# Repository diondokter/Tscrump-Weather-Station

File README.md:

# Tscrump-Weather-Station
Project for making a weather station.

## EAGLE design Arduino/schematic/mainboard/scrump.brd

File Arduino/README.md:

The bootloader is the exact same as the Adafruit M0 feather.
You will need to install the SAMD board toolchain from Adafruit in your Arduino IDE to compile and upload.
Instructions can be found [here](https://learn.adafruit.com/adafruit-feather-m0-basic-proto/using-with-arduino-ide).

You will need the following libraries:
- TheThingsNetwork 2.0.0 (2.1+ breaks non-AVR compatibility)
- Adafruit Unified Sensor 1.0.2
- DHT sensor library 1.3.0+
- Adafruit BMP085 Unified 1.0.0+

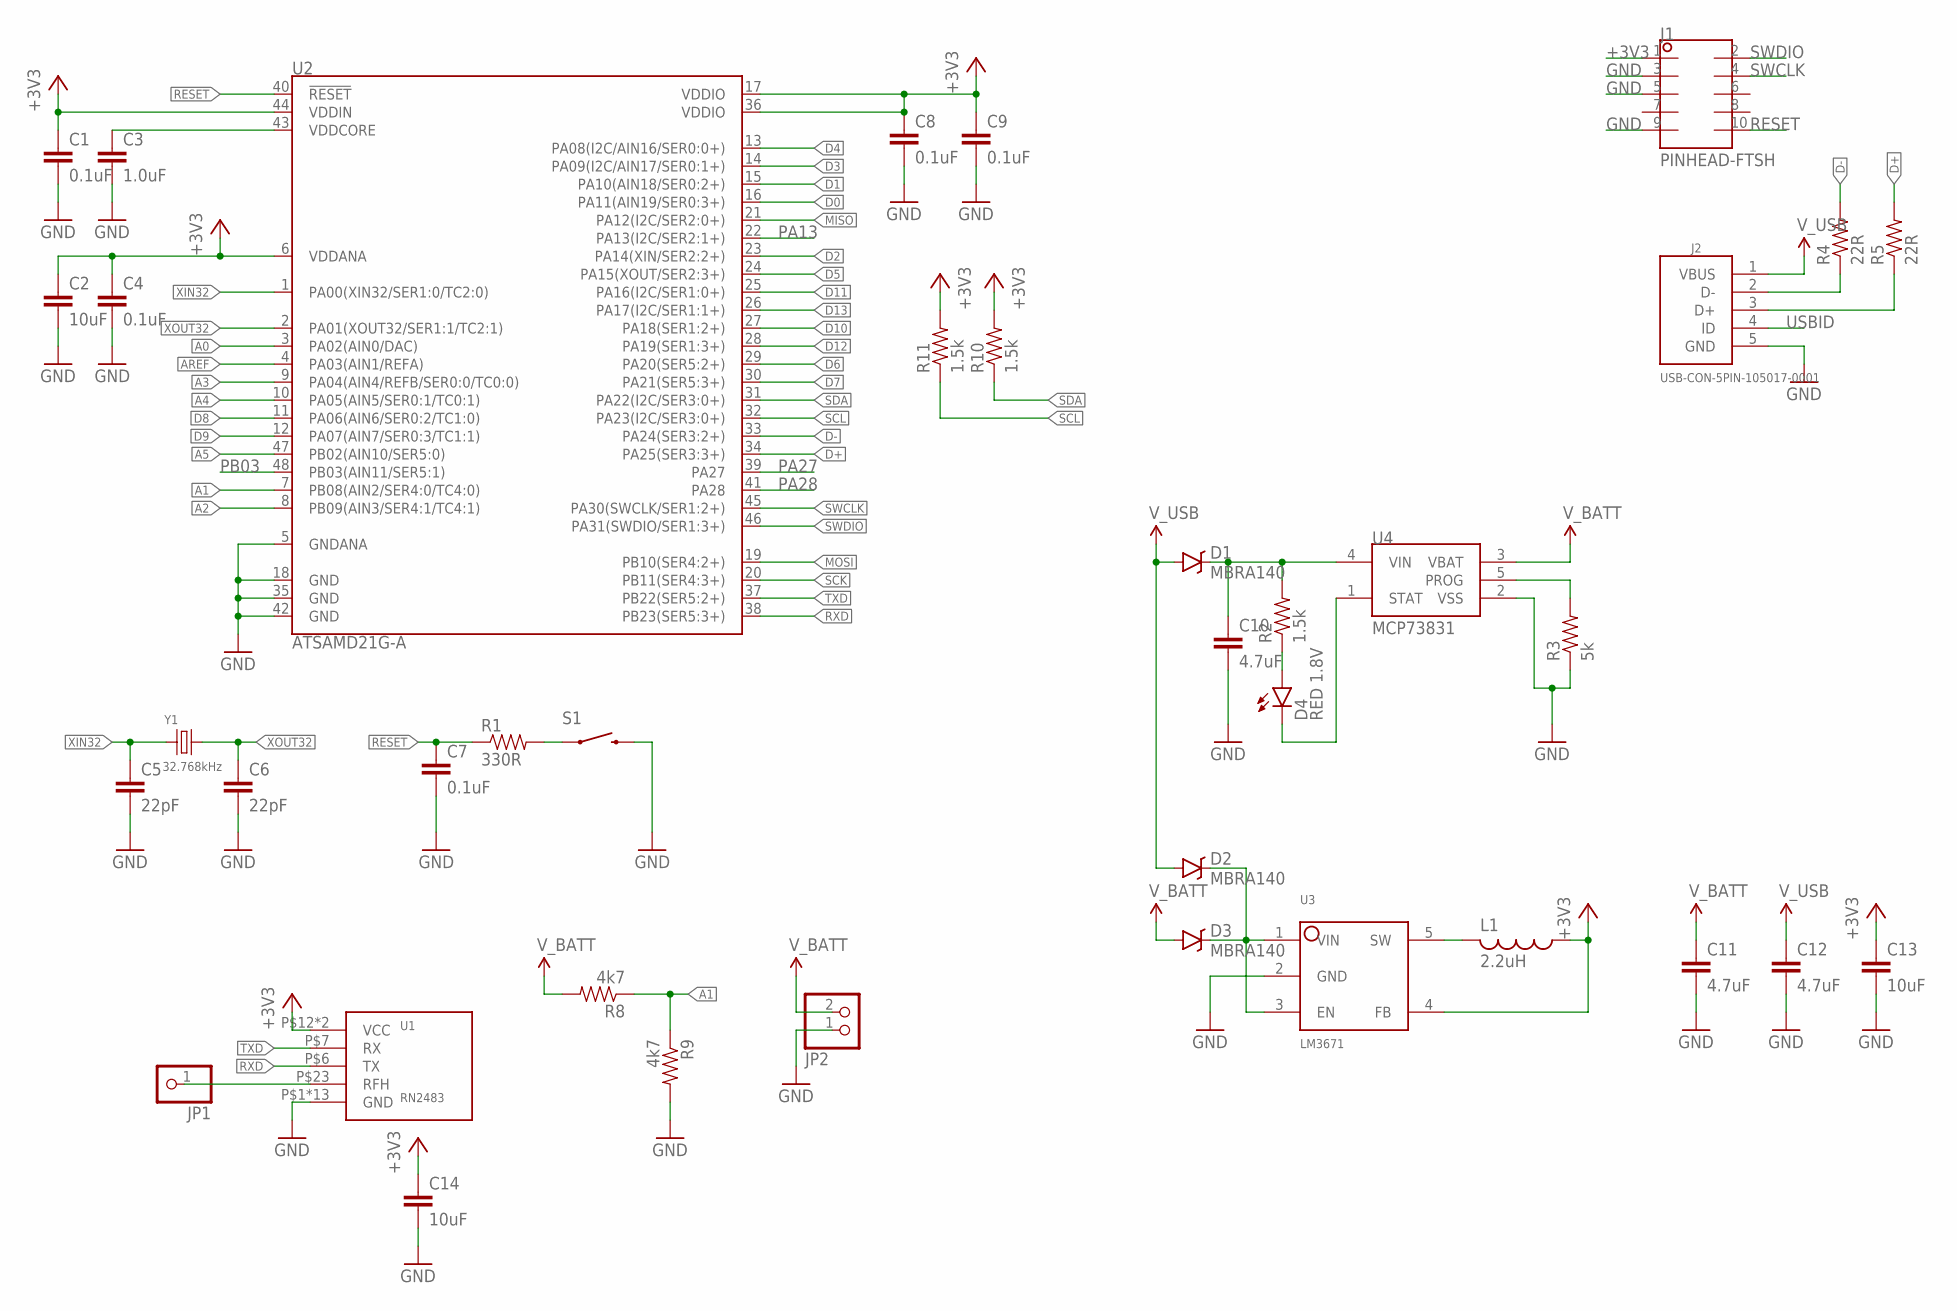
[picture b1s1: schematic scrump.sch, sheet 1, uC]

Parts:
C1, C4, C7, C8, C9: 0.1uF; 0603-CAP
C2, C13, C14: 10uF; 0603-CAP
C3: 1.0uF; 0603-CAP
C5, C6: 22pF; 0603-CAP
C10, C11, C12: 4.7uF; 0603-CAP
D1, D2, D3: MBRA140; SMA-DIODE
D4: RED 1.8V; LED-0603
J1: PINHEAD-FTSH; FTSH-105-01-XXX-DV-K
J2: USB-CON-5PIN-105017-0001; USB-MICRO-MOLEX-105017-0001
JP1: PINHD-1X1; 1X01
JP2: PINHD-1X2; 1X02
L1: 2.2uH; 0806-INDUCTOR
R1: 330R; 0603-RES
R2, R10, R11: 1.5k; 0603-RES
R3: 5k; 0603-RES
R4, R5: 22R; 0603-RES
R8, R9: 4k7; 0603-RES
S1: PUSHBUTTON-SMD; TACTILE-SMD-SWITCH
U1: RN2483
U2: ATSAMD21G-A; TQFP-48
U3: LM3671; SOT23-5
U4: MCP73831; SOT23-5
Y1: 32.768kHz; ABS25

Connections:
+3V3: C1.1, C2.1, C4.1, C8.1, C9.1, C13.1, C14.1, J1.1, L1.1, R10.2, R11.2, U1.P$12 (VCC), U1.P$34 (VCC), U2.6 (VDDANA), U2.17 (VDDIO), U2.36 (VDDIO), U2.44 (VDDIN), U3.4 (FB); also elsewhere on the board
A0: U2.3 (PA02(AIN0/DAC)); also elsewhere on the board
A1: R8.1, R9.1, U2.7 (PB08(AIN2/SER4:0/TC4:0))
A2: U2.8 (PB09(AIN3/SER4:1/TC4:1))
A3: U2.9 (PA04(AIN4/REFB/SER0:0/TC0:0))
A4: U2.10 (PA05(AIN5/SER0:1/TC0:1))
A5: U2.47 (PB02(AIN10/SER5:0))
AREF: U2.4 (PA03(AIN1/REFA))
D0: U2.16 (PA11(AIN19/SER0:3+))
D1: U2.15 (PA10(AIN18/SER0:2+))
D2: U2.23 (PA14(XIN/SER2:2+))
D3: U2.14 (PA09(I2C/AIN17/SER0:1+))
D4: U2.13 (PA08(I2C/AIN16/SER0:0+)); also elsewhere on the board
D5: U2.24 (PA15(XOUT/SER2:3+))
D6: U2.29 (PA20(SER5:2+))
D7: U2.30 (PA21(SER5:3+))
D8: U2.11 (PA06(AIN6/SER0:2/TC1:0))
D9: U2.12 (PA07(AIN7/SER0:3/TC1:1))
D10: U2.27 (PA18(SER1:2+))
D11: U2.25 (PA16(I2C/SER1:0+))
D12: U2.28 (PA19(SER1:3+))
D13: U2.26 (PA17(I2C/SER1:1+))
D+: R5.2, U2.34 (PA25(SER3:3+))
D-: R4.2, U2.33 (PA24(SER3:2+))
GND: C1.2, C2.2, C3.2, C4.2, C5.2, C6.2, C7.2, C8.2, C9.2, C10.2, C11.2, C12.2, C13.2, C14.2, J1.3, J1.5, J1.9, J2.5 (GND), JP2.1, R3.1, R9.2, S1.P$3 (2), S1.P$4 (2), U1.P$1 (GND), U1.P$8 (GND), U1.P$11 (GND), U1.P$20 (GND), U1.P$21 (GND), U1.P$22 (GND), U1.P$24 (GND), U1.P$26 (GND), U1.P$27 (GND), U1.P$28 (GND), U1.P$33 (GND), U1.P$41 (GND), U1.P$47 (GND), U2.5 (GNDANA), U2.18 (GND), U2.35 (GND), U2.42 (GND), U3.2 (GND), U4.2 (VSS); also elsewhere on the board
MISO: U2.21 (PA12(I2C/SER2:0+))
MOSI: U2.19 (PB10(SER4:2+))
unnamed: C3.1, U2.43 (VDDCORE)
unnamed: R1.2, S1.P$1 (1), S1.P$2 (1)
unnamed: C10.1, D1.C, R2.2, U4.4 (VIN)
unnamed: J2.3 (D+), R5.1
unnamed: L1.2, U3.5 (SW)
unnamed: D4.C, U4.1 (STAT)
unnamed: D4.A, R2.1
unnamed: R3.2, U4.5 (PROG)
unnamed: J2.2 (D-), R4.1
unnamed: D2.C, D3.C, U3.1 (VIN), U3.3 (EN)
unnamed: JP1.1, U1.P$23 (RFH)
PA13: U2.22 (PA13(I2C/SER2:1+))
PA27: U2.39 (PA27)
PA28: U2.41 (PA28)
PB03: U2.48 (PB03(AIN11/SER5:1))
RESET: C7.1, J1.10, R1.1, U2.40 (!RESET!)
RXD: U1.P$6 (TX), U2.38 (PB23(SER5:3+))
SCK: U2.20 (PB11(SER4:3+))
SCL: R11.1, U2.32 (PA23(I2C/SER3:0+)); also elsewhere on the board
SDA: R10.1, U2.31 (PA22(I2C/SER3:0+)); also elsewhere on the board
SWCLK: J1.4, U2.45 (PA30(SWCLK/SER1:2+))
SWDIO: J1.2, U2.46 (PA31(SWDIO/SER1:3+))
TXD: U1.P$7 (RX), U2.37 (PB22(SER5:2+))
USBID: J2.4 (ID)
V_BATT: C11.1, D3.A, JP2.2, R8.2, U4.3 (VBAT)
V_USB: C12.1, D1.A, D2.A, J2.1 (VBUS)
XIN32: C5.1, U2.1 (PA00(XIN32/SER1:0/TC2:0)), Y1.P$1 (1)
XOUT32: C6.1, U2.2 (PA01(XOUT32/SER1:1/TC2:1)), Y1.P$4 (3)

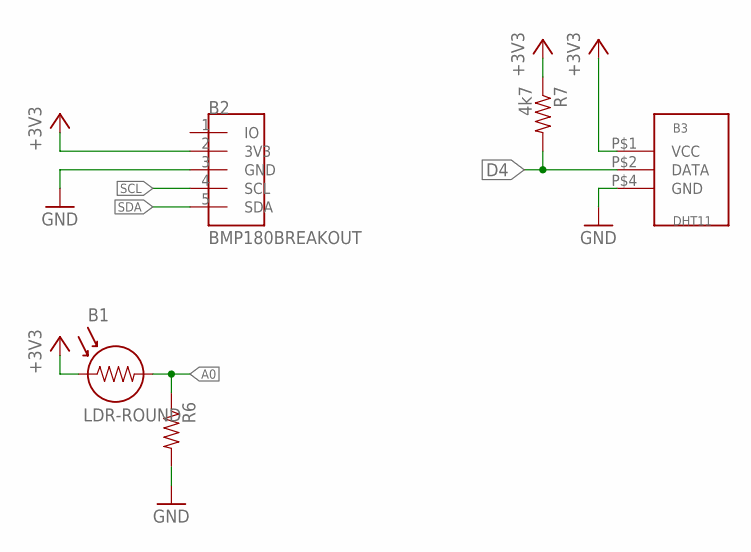
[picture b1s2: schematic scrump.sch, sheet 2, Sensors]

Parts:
B1: LDR-ROUND
B2: BMP180BREAKOUT; BMP180_BREAKOUT
B3: DHT11
R6: RESISTOR0603; 0603-RES
R7: 4k7; 0603-RES

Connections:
+3V3: B1.P$1 (1), B2.2 (3V3), B3.P$1 (VCC), R7.1; also elsewhere on the board
A0: B1.P$2 (2), R6.1; also elsewhere on the board
D4: B3.P$2 (DATA), R7.2; also elsewhere on the board
GND: B2.3 (GND), B3.P$4 (GND), R6.2; also elsewhere on the board
SCL: B2.4 (SCL); also elsewhere on the board
SDA: B2.5 (SDA); also elsewhere on the board

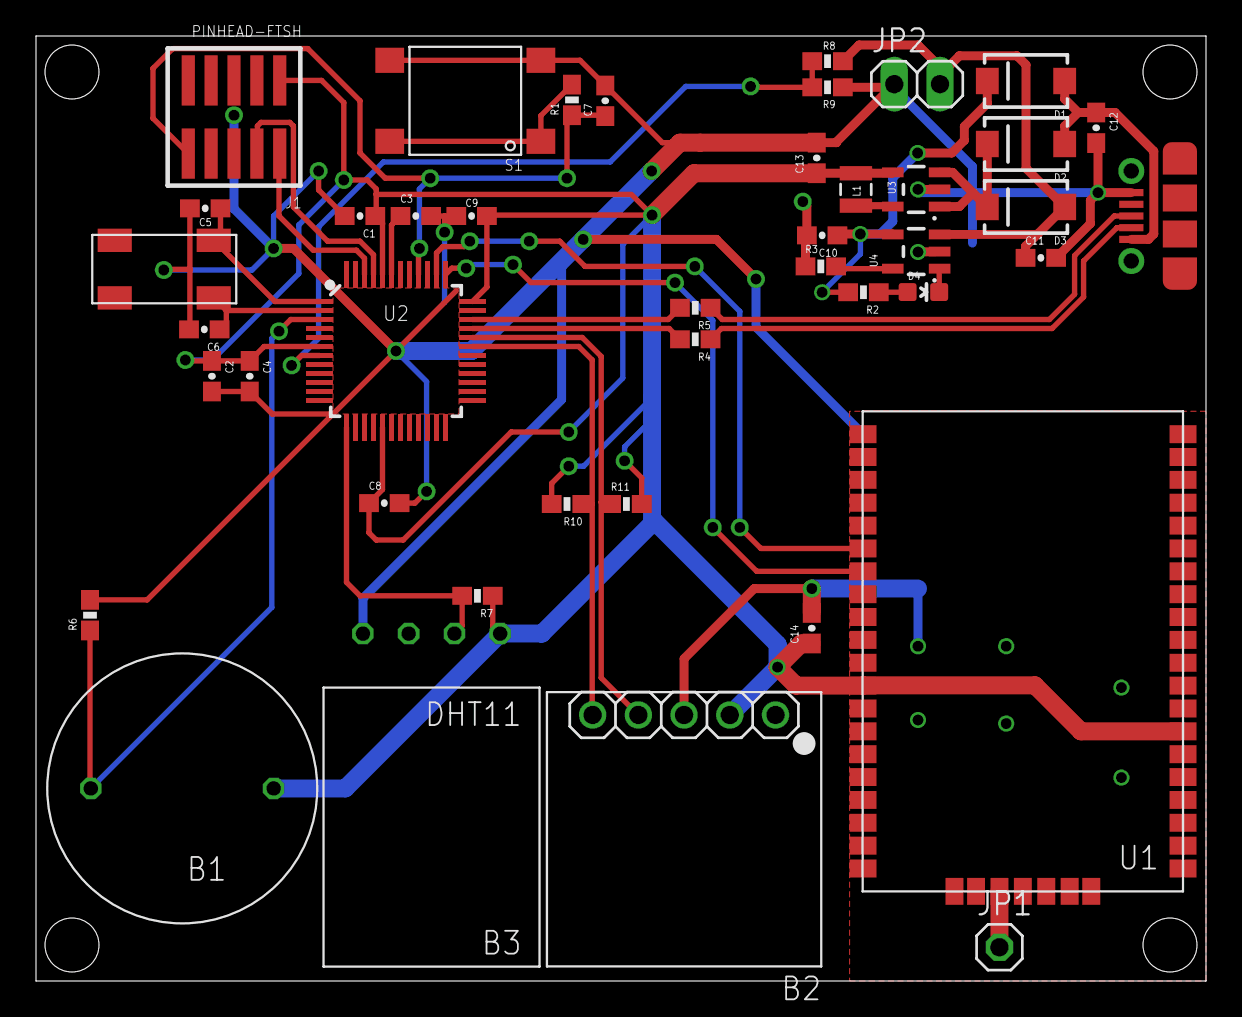
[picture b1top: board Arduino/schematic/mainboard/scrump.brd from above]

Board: 2 copper layers, 65.0 x 52.5 mm, 43 parts (0 on the bottom side), 29 nets.

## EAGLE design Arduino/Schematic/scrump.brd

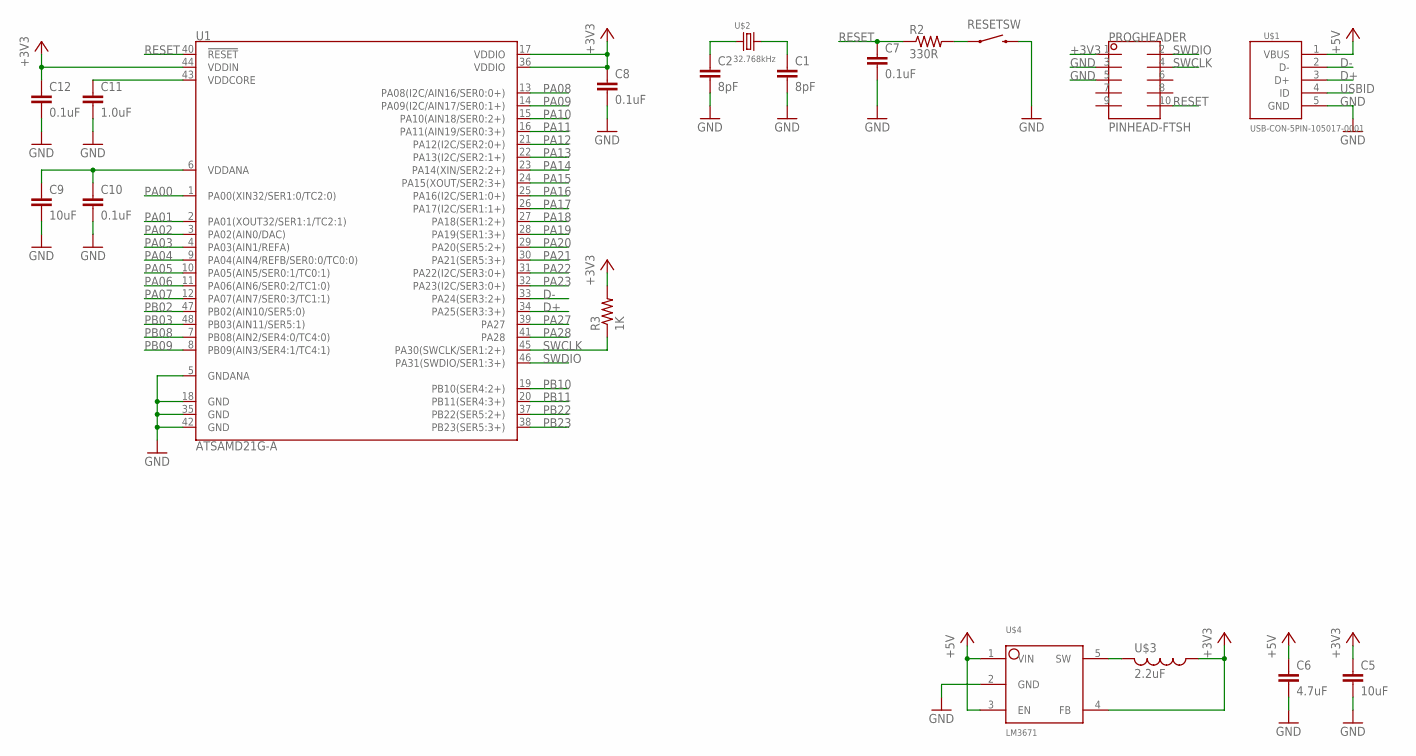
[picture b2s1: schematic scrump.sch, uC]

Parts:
C1, C2: 8pF; 0603-CAP
C5, C9: 10uF; 0603-CAP
C6: 4.7uF; 0603-CAP
C7, C8, C10, C12: 0.1uF; 0603-CAP
C11: 1.0uF; 0603-CAP
PROGHEADER: PINHEAD-FTSH; FTSH-105-01-XXX-DV-K
R2: 330R; 0603-RES
R3: 1K; 0603-RES
RESETSW: PUSHBUTTON-SMD; TACTILE-SMD-SWITCH
U1: ATSAMD21G-A; TQFP-48
U$1: USB-CON-5PIN-105017-0001; USB-MICRO-MOLEX-105017-0001
U$2: 32.768kHz; ABS25
U$3: 2.2uF; 0806-INDUCTOR
U$4: LM3671; SOT23-5

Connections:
+3V3: C5.1, C8.1, C12.1, PROGHEADER.1, R3.2, U1.17 (VDDIO), U1.36 (VDDIO), U1.44 (VDDIN), U$3.1, U$4.4 (FB)
+5V: C6.1, U$1.1 (VBUS), U$4.1 (VIN), U$4.3 (EN)
D+: U1.34 (PA25(SER3:3+)), U$1.3 (D+)
D-: U1.33 (PA24(SER3:2+)), U$1.2 (D-)
GND: C1.2, C2.2, C5.2, C6.2, C7.2, C8.2, C9.2, C10.2, C11.2, C12.2, PROGHEADER.3, PROGHEADER.5, RESETSW.P$3 (2), RESETSW.P$4 (2), U1.5 (GNDANA), U1.18 (GND), U1.35 (GND), U1.42 (GND), U$1.5 (GND), U$4.2 (GND)
unnamed: C11.1, U1.43 (VDDCORE)
unnamed: R2.2, RESETSW.P$1 (1), RESETSW.P$2 (1)
unnamed: C9.1, C10.1, U1.6 (VDDANA)
unnamed: U$3.2, U$4.5 (SW)
PA00: C2.1, U1.1 (PA00(XIN32/SER1:0/TC2:0)), U$2.P$1 (1)
PA01: C1.1, U1.2 (PA01(XOUT32/SER1:1/TC2:1)), U$2.P$4 (3)
PA02: U1.3 (PA02(AIN0/DAC))
PA03: U1.4 (PA03(AIN1/REFA))
PA04: U1.9 (PA04(AIN4/REFB/SER0:0/TC0:0))
PA05: U1.10 (PA05(AIN5/SER0:1/TC0:1))
PA06: U1.11 (PA06(AIN6/SER0:2/TC1:0))
PA07: U1.12 (PA07(AIN7/SER0:3/TC1:1))
PA08: U1.13 (PA08(I2C/AIN16/SER0:0+))
PA09: U1.14 (PA09(I2C/AIN17/SER0:1+))
PA10: U1.15 (PA10(AIN18/SER0:2+))
PA11: U1.16 (PA11(AIN19/SER0:3+))
PA12: U1.21 (PA12(I2C/SER2:0+))
PA13: U1.22 (PA13(I2C/SER2:1+))
PA14: U1.23 (PA14(XIN/SER2:2+))
PA15: U1.24 (PA15(XOUT/SER2:3+))
PA16: U1.25 (PA16(I2C/SER1:0+))
PA17: U1.26 (PA17(I2C/SER1:1+))
PA18: U1.27 (PA18(SER1:2+))
PA19: U1.28 (PA19(SER1:3+))
PA20: U1.29 (PA20(SER5:2+))
PA21: U1.30 (PA21(SER5:3+))
PA22: U1.31 (PA22(I2C/SER3:0+))
PA23: U1.32 (PA23(I2C/SER3:0+))
PA27: U1.39 (PA27)
PA28: U1.41 (PA28)
PB02: U1.47 (PB02(AIN10/SER5:0))
PB03: U1.48 (PB03(AIN11/SER5:1))
PB08: U1.7 (PB08(AIN2/SER4:0/TC4:0))
PB09: U1.8 (PB09(AIN3/SER4:1/TC4:1))
PB10: U1.19 (PB10(SER4:2+))
PB11: U1.20 (PB11(SER4:3+))
PB22: U1.37 (PB22(SER5:2+))
PB23: U1.38 (PB23(SER5:3+))
RESET: C7.1, PROGHEADER.10, R2.1, U1.40 (!RESET!)
SWCLK: PROGHEADER.4, R3.1, U1.45 (PA30(SWCLK/SER1:2+))
SWDIO: PROGHEADER.2, U1.46 (PA31(SWDIO/SER1:3+))
USBID: U$1.4 (ID)

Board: 2 copper layers, 19 parts (0 on the bottom side), 14 nets, no tracks yet.

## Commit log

2016-11-16 Start project structure. - Added gitignores - Added Project Plan document
2016-11-18 First Xamarin Setup
2016-11-18 DHT-sensor-library
2016-11-18 BMP180
2016-11-18 Added first database management. - Updated some components
2016-11-19 UWP database connection now works in LAN.
2016-11-19 added LoRa libraries
2016-11-19 added arduino code for the BMP180
2016-11-19 Added a dummy database
2016-11-19 Preparations for drawing graphs.
2016-11-20 added deployment script
    Dit script zorgt ervoor dat de site automatisch update wanneer master word geupdate
2016-11-20 Now using a webview and html for creating the graph
2016-11-20 Experiments with WebView
2016-11-21 De complete website met alle mikmak erbij.
2016-11-21 MySQL Connector now gets saved. (Change in GitIgnore)
2016-11-21 Removed Webview for charts
2016-11-21 changed header
2016-11-21 changed some spelling mistakes
2016-11-21 Changed de dbname into dummyweatherstation
2016-11-21 changed the dbname
2016-11-21 Added Project Plan Document
2016-11-21 Cleanup, removed examples
2016-11-22 Removed webview chart and started on custom Oxyplot solution
2016-11-22 changed copyright
2016-11-22 Deleted deploy.php
    This was suposed to be used for automatic deployment but never worked. We now do it with a pull from crontab
2016-11-23 changed the table name
2016-11-23 Needed for sourcetree
2016-11-23 Changed text and changed table searched in by the sql query
2016-11-24 test
2016-11-24 Added a new Database File
    For testing with with the Graph's.
2016-11-24 A new test file for Graph's
    New Graph file for testing with the database, as it is not working now.
2016-11-24 TTN Lora library updated
2016-11-24 deleted corrupted libraries
2016-11-24 Removing previous attempts of creating a chart to prepare for Syncfusion
2016-11-24 Short readme about function of library
2016-11-24 New Website with working Graph's
2016-11-24 Added Syncfusion library for charts
2016-11-24 Update GraphBrightness.php
    Changed font so the Graph's may work.
2016-11-24 Added readme for DHT11
2016-11-24 Graph working on UWP with syncfusion
2016-11-25 Changed the site so that it will work for mobile phone's.
2016-11-25 Made changes to the website so that it will work for mobile devices.
2016-11-25 Fixed small bugs that appeared with previous push.
2016-11-25 Improved axis
2016-11-25 Chart is now on its own page. Also started using NavigationPage.
2016-11-25 Updated gitignore
2016-11-25 Throwing the mess in the bin
2016-11-25 Added the initial schematics
2016-11-26 Did some file management, deleted a whole lot of files and moved others to more appropiate locations.
2016-11-26 Forgot to change the database login credentials back to the project one, changed it.
2016-11-27 Added update method for the chart
2016-11-27 new dht11 library provided by DFRobot
    since the adafruit library didnt work well i found a new library that works well with the our sensor.
2016-11-27 First version of database availability check
2016-11-28 Java application that connects to a Mqtt broker
    There are 3 classes:
    1- PahoDemo class
    2- PahoMqttCleint class: which is a class that uses Paho to connect to any broker
    3- Main class: this class was used to test the TTN java library.
2016-11-28 Changed the url's because the picture's weren't working.
2016-11-28 Added the initial schematics - Added BOM and library - Schematics in their own folder - Added gitignore - Added battery option to board
2016-11-29 Changed the x-axis titless
2016-11-29 Updateded Config.php
    Because the inlog credentials were wrong.
2016-11-29 Started on adding advanced chart controlls
2016-11-30 Fixed issues after review - Missing 3.3V line on Vddana - Added decoupling cap for second vddio - Removed pull-up on swdclk, which is usually included in the programmer itself. - Added 22 ohm resisto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
2016-12-01 Better error handling when there's no database connection
2016-12-01 Graph's values added and wiki page updated
2016-12-01 Added DHT11
2016-12-01 More work on advanced options for chart. Database connects to the server now.
2016-12-05 Advanced Chart Options now done. Bug, line visibility doesn't always work after opening advanced options.
2016-12-05 Added community and official LoRa libraries
2016-12-05 fixed folder location
2016-12-05 Fixed link to wiki
    Title says it all
2016-12-08 Made prettier and first development for Android
2016-12-12 Added gui and DBmanager with some fixes to the mqtt class
2016-12-12 tippingbucket code
2016-12-12 full commit of code and a note.
    This code lacks a function that sends the amount of rain that has fallen (equal to the product of mmpertip and tipCounter) over the LoRa network, and then resets the tipCounter variable. This is depe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
2016-12-12 tippingbucket code 2
2016-12-16 fixed some gui issues
2016-12-18 fixed the exception of the connection
2016-12-19 Updated the Temperature Graph
    Fixed it so that the negative value's of the temperature will work aswell!
2016-12-19 Fixed the website layout for mobile
    When using landscape mode with mobile telephone the graph would glitch out.
2016-12-19 semi-final change
2017-01-07 Final version: - Fixed power delivery - Added sensors - Minor changes to schematic - Completed PCB - Used for production
2017-01-09 Add files via upload
    uploaded a picture for 'Project Structure'
2017-01-09 Added more comments and added support for Android
2017-01-12 Added comments to the codings and removed some unneccesary files.
2017-01-12 Restored the src files because it wasn't working on the site while it was working on localhost.
2017-01-12 Another commit just to check wether it are the graph files or not
2017-01-12 Retry
2017-01-12 Added the config
2017-01-12 Fixed the anti-aliasing bug
2017-01-12 SRC files fix.
2017-01-15 Final BOM - Added passive components - Changed the power inductor(out of stock)
2017-01-15 remote acces to databes granted
2017-01-16 Fixed some little stuff
2017-01-17 the DB insert is more dynamic now and weatherDAO is a function in PahoMqttClient
2017-01-17 tmp2
2017-01-18 Nog een tekening voor de wiki
    staat momenteel op imgur, maar is beter als alles op github staat.
2017-01-18 Working LoRa
2017-01-19 parsing
2017-01-19 update parsing and added new gui function
2017-01-19 Working version
2017-01-19 reciving data from new arduino code
2017-01-20 db tests added
2017-01-20 Changed pressure tag from bar to hPa
2017-01-20 full consol program
2017-02-02 Fixed wrong merge
2017-02-02 Added a picture to use on the wiki. Doesn't need to be pushed to master.
2017-02-02 Added picture of app to use on wiki. No need add to master.
2017-02-02 Added picture for rainmeter. No need to add to master.

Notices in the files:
parts and their libraries:
SparkFun-Capacitors: Licensing: Creative Commons ShareAlike 4.0 International - https://creativecommons.org/licenses/by-sa/4.0
